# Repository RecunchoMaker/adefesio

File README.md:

# adefesio

**adefesio** intentará ser un pequeno robot para iniciarse na competición da resolución de
de labirintos. Está baseado en componentes de baixo custe (arduino, motores micrometal...)
e polo tanto a intención do proxecto non é facer un robot competitivo, senón explorar
e investigar os desfíos de programación que aparecen nesta competición.

## making off

En [Adefesio blog](https://recunchomaker.github.io/adefesio/) estamos facendo un
blog co progreso do proxecto.

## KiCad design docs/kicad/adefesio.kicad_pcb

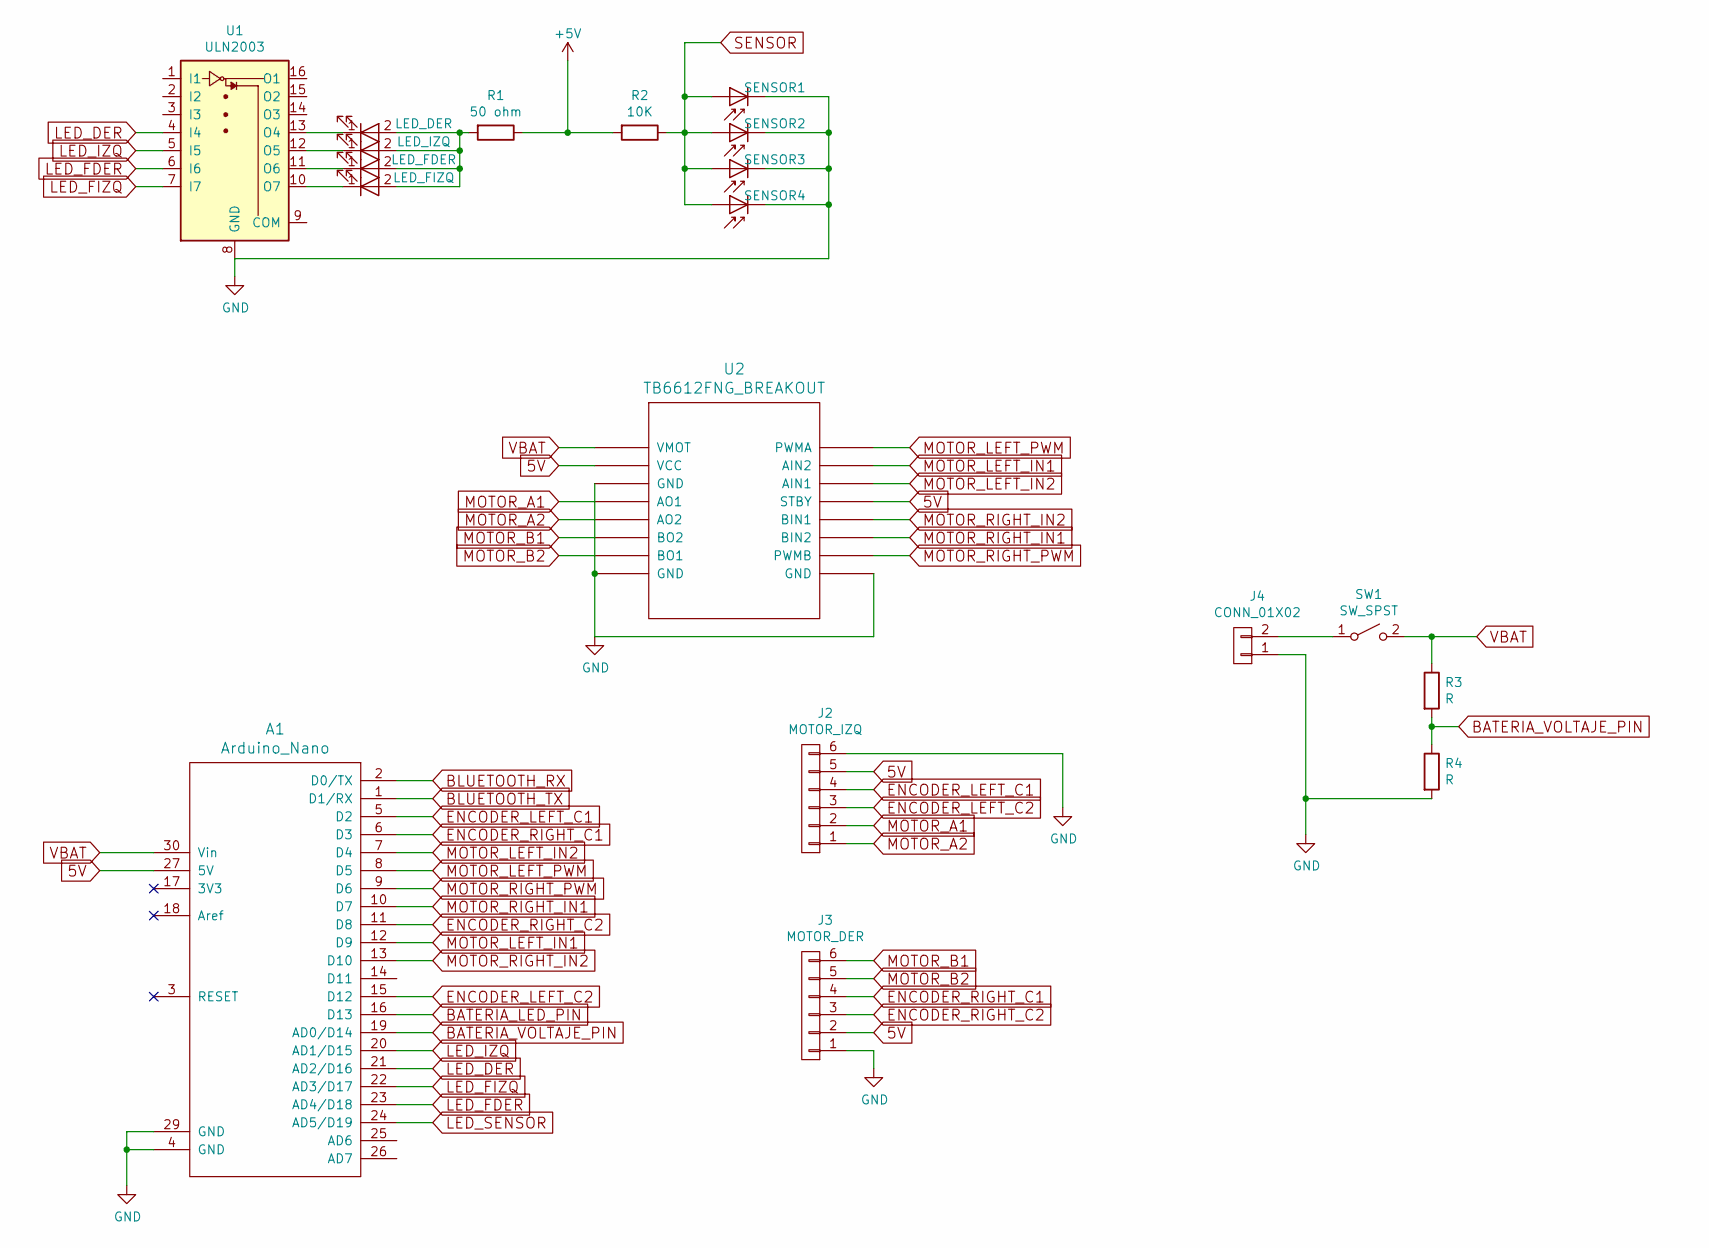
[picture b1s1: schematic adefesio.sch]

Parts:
A1: Arduino_Nano; arduino_nano
D1: LED_DER; LED_D1.8mm_W1.8mm_H2.4mm_Horizontal_O6.35mm_Z1.6mm
D2: SENSOR1; LED_D1.8mm_W1.8mm_H2.4mm_Horizontal_O3.81mm_Z1.6mm
D3: LED_IZQ; LED_D1.8mm_W1.8mm_H2.4mm_Horizontal_O6.35mm_Z1.6mm
D4: LED_FDER; LED_D1.8mm_W1.8mm_H2.4mm_Horizontal_O6.35mm_Z1.6mm
D5: LED_FIZQ; LED_D1.8mm_W1.8mm_H2.4mm_Horizontal_O6.35mm_Z1.6mm
D6: SENSOR2; LED_D1.8mm_W1.8mm_H2.4mm_Horizontal_O3.81mm_Z1.6mm
D7: SENSOR3; LED_D1.8mm_W1.8mm_H2.4mm_Horizontal_O3.81mm_Z1.6mm
D8: SENSOR4; LED_D1.8mm_W1.8mm_H2.4mm_Horizontal_O3.81mm_Z1.6mm
J2: MOTOR_IZQ; PINHEAD1-6
J3: MOTOR_DER; PINHEAD1-6
J4: CONN_01X02; PINHEAD1-2
R1: 50 ohm; R_Axial_DIN0207_L6.3mm_D2.5mm_P10.16mm_Horizontal
R2: 10K; R_Axial_DIN0207_L6.3mm_D2.5mm_P10.16mm_Horizontal
R3, R4: R; R_Axial_DIN0204_L3.6mm_D1.6mm_P7.62mm_Horizontal
SW1: SW_SPST; SW_DIP_x1_W7.62mm_Slide_Copal_CHS-B
U1: ULN2003; DIP-16_W7.62mm_LongPads
U2: TB6612FNG_BREAKOUT; DIP-16_600

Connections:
5V: A1.27 (5V), J2.5, J3.2, U2.2 (VCC), U2.13 (STBY)
+5V: R1.1, R2.2
BATERIA_LED_PIN: A1.16 (D13)
BATERIA_VOLTAJE_PIN: A1.19 (AD0/D14), R3.2, R4.1
BLUETOOTH_RX: A1.2 (D0/TX)
BLUETOOTH_TX: A1.1 (D1/RX)
ENCODER_LEFT_C1: A1.5 (D2), J2.4
ENCODER_LEFT_C2: A1.15 (D12), J2.3
ENCODER_RIGHT_C1: A1.6 (D3), J3.4
ENCODER_RIGHT_C2: A1.11 (D8), J3.3
GND: A1.4 (GND), A1.29 (GND), D2.1 (K), D6.1 (K), D7.1 (K), D8.1 (K), J2.6, J3.1, J4.1, R4.2, U1.8 (GND), U2.3 (GND), U2.8 (GND), U2.9 (GND)
LED_DER: A1.21 (AD2/D16), U1.4 (I4)
LED_FDER: A1.23 (AD4/D18), U1.6 (I6)
LED_FIZQ: A1.22 (AD3/D17), U1.7 (I7)
LED_IZQ: A1.20 (AD1/D15), U1.5 (I5)
LED_SENSOR: A1.24 (AD5/D19)
MOTOR_A1: J2.2, U2.4 (AO1)
MOTOR_A2: J2.1, U2.5 (AO2)
MOTOR_B1: J3.6, U2.6 (BO2)
MOTOR_B2: J3.5, U2.7 (BO1)
MOTOR_LEFT_IN1: A1.12 (D9), U2.15 (AIN2)
MOTOR_LEFT_IN2: A1.7 (D4), U2.14 (AIN1)
MOTOR_LEFT_PWM: A1.8 (D5), U2.16 (PWMA)
MOTOR_RIGHT_IN1: A1.10 (D7), U2.11 (BIN2)
MOTOR_RIGHT_IN2: A1.13 (D10), U2.12 (BIN1)
MOTOR_RIGHT_PWM: A1.9 (D6), U2.10 (PWMB)
unnamed: D1.1 (K), U1.13 (O4)
unnamed: D1.2 (A), D3.2 (A), D4.2 (A), D5.2 (A), R1.2
unnamed: D3.1 (K), U1.12 (O5)
unnamed: D4.1 (K), U1.11 (O6)
unnamed: D5.1 (K), U1.10 (O7)
unnamed: J4.2, SW1.1 (A)
SENSOR: D2.2 (A), D6.2 (A), D7.2 (A), D8.2 (A), R2.1
VBAT: A1.30 (Vin), R3.1, SW1.2 (B), U2.1 (VMOT)

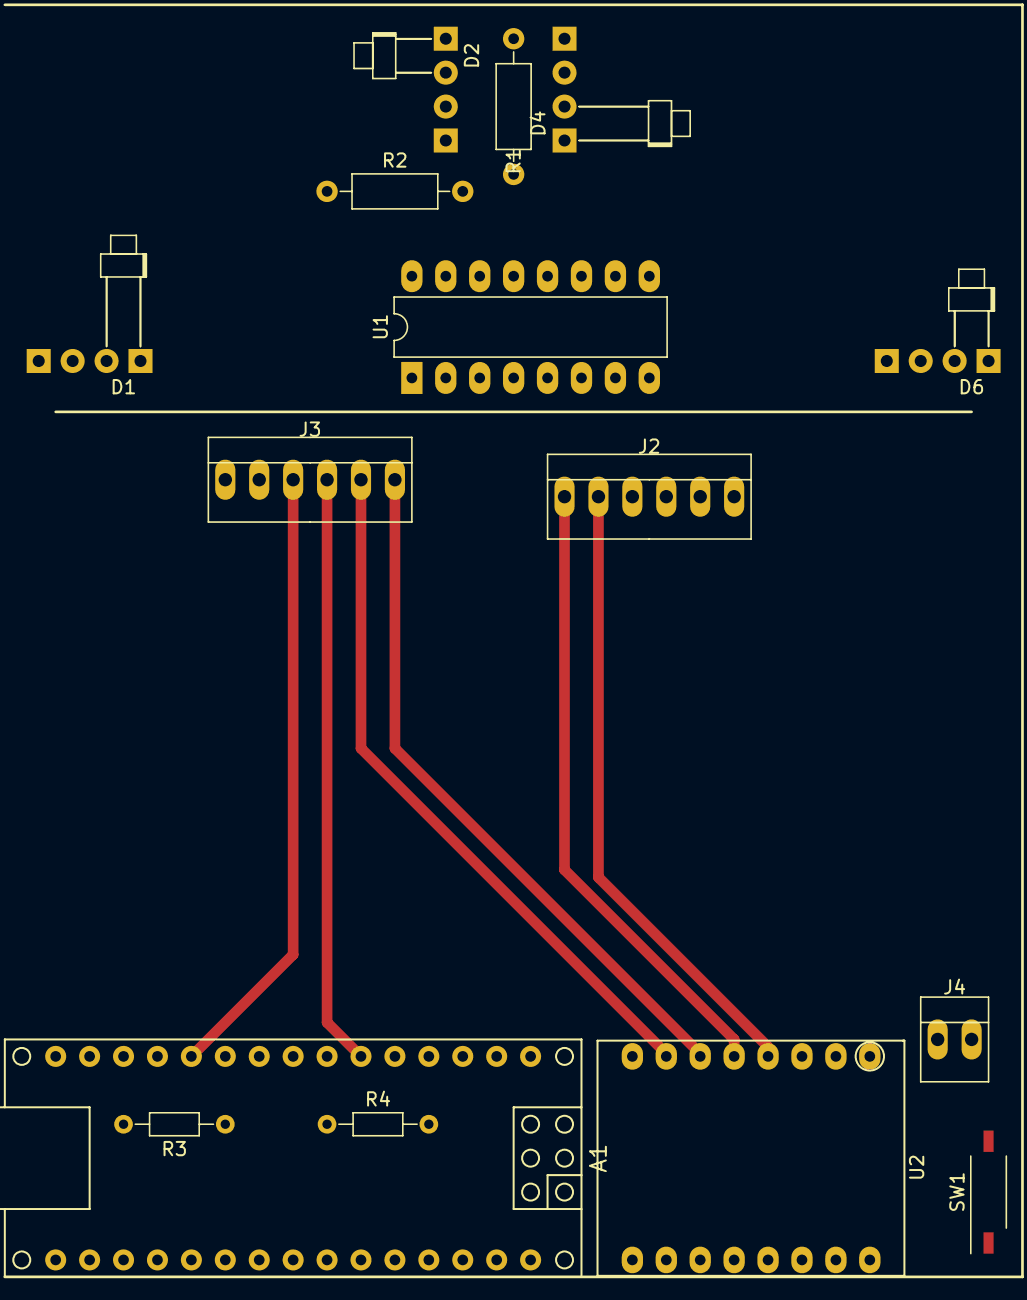
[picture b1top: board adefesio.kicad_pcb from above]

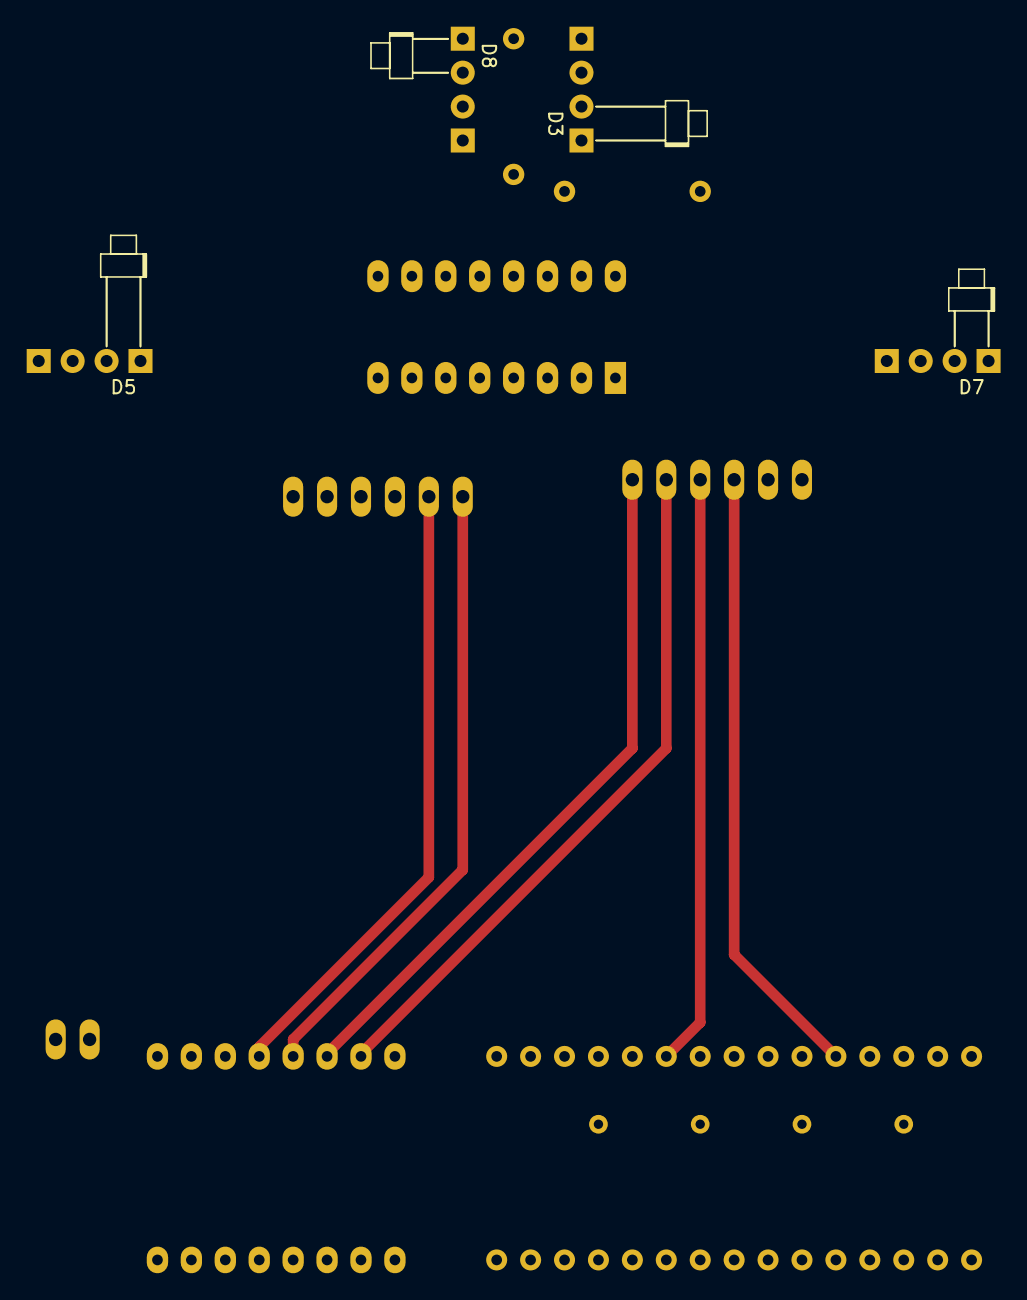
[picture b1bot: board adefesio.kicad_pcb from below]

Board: 2 copper layers, 19 parts (4 on the bottom side), 30 nets.

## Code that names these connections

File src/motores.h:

/**
 * @file motores.h
 *
 * @brief Cabecera de motores.cpp
 */

#ifndef __MOTORES_H
#define __MOTORES_H

#include <encoders.h>

//@{
/**
 * @name Pins del puente H
 */

#define MOTOR_LEFT_PWM 5   ///< Pin digital de salida PWM izquierdo 
#define MOTOR_LEFT_IN1 4   ///< Pin digital de salida IN1 izquierdo 
#define MOTOR_LEFT_IN2 9   ///< Pin digital de salida IN1 izquierdo 

#define MOTOR_RIGHT_PWM 6  ///< Pin digital de salida PWM izquierdo 
#define MOTOR_RIGHT_IN1 7  ///< Pin digital de salida IN1 derecho
#define MOTOR_RIGHT_IN2 10 ///< Pin digital de salida IN2 derecho
//@}

// TODO: fix this
#define GIRO_IZQUIERDA_TODO 0
#define GIRO_DERECHA_TODO   0.01

void motores_init(float voltaje);
void motores_set_potencia(float left, float right);
void motores_set_pwm_left(int16_t right);
void motores_set_pwm_right(int16_t left);
void motores_parar();
void motores_actualiza_velocidad();

float motores_get_kp_lineal();
void motores_set_kp_lineal(float kp);
float motores_get_ki_lineal();
void motores_set_ki_lineal(float ki);
float motores_get_kd_lineal();
void motores_set_kd_lineal(float kd);
float motores_get_kp_pasillo1();
void motores_set_kp_pasillo1(float kd);
float motores_get_kp_pasillo2();
void motores_set_kp_pasillo2(float kd);

float motores_get_velocidad_lineal_objetivo();
float motores_get_velocidad_lineal_objetivo_left();
float motores_get_velocidad_lineal_objetivo_right();
float motores_get_radio();
void motores_set_velocidad_lineal_objetivo(float velocidad);

int16_t motores_get_pwm_left();
int16_t motores_get_pwm_right();

void motores_set_maximo_pwm(int16_t pwm);
float motores_get_velocidad_angular_objetivo();
float motores_get_distancia_entre_ruedas();
void motores_set_distancia_entre_ruedas(float dr);

float motores_get_aceleracion_lineal();
void motores_set_aceleracion_lineal(float aceleracion);

void motores_set_radio(float r);

#endif /* ifndef MOTORES_H

 */

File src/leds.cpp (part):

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 * @brief Funciones para controlar los leds/sensores infrarrojos
 *
 * Los leds infrarrojos se controlan individualmente, cada uno con un
 * pin digital de salida, y hay un único sensor de entrada en un pin analógico. 
 *
 * Los pins que activan los diodos digitales deben ser adyacentes en el procesador, 
 * para facilitar la aritmética a la hora de almacenar valores en los arrays.
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
void leds_init() {

    pinMode(LED_IZQ, OUTPUT);
    pinMode(LED_DER, OUTPUT);
    pinMode(LED_FIZQ, OUTPUT);
    pinMode(LED_FDER, OUTPUT);

    pinMode(LED_SENSOR, INPUT);

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
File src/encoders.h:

/**
 * @file encoders.h
 *
 * @brief Cabecera de encoders.cpp
 */

#ifndef __ENCODERS_H
#define __ENCODERS_H

#include <Arduino.h>

#define ENCODER_LEFT_C1 2
#define ENCODER_LEFT_C2 12
#define ENCODER_RIGHT_C1 3
#define ENCODER_RIGHT_C2 8

void encoders_init(void);

void encoders_reset_posicion(void);
void encoders_reset_posicion_total(void);
void encoders_reset_posicion_aux_total(void);
void encoders_decrementa_posicion_total(int16_t pasos);

int32_t encoders_get_posicion_total_left(void);
int32_t encoders_get_posicion_total_right(void);
int32_t encoders_get_posicion_aux_left(void);
int32_t encoders_get_posicion_aux_right(void);
int32_t encoders_get_posicion_aux(void);

uint8_t encoders_get_ticks_sin_actualizar_left(void);
uint8_t encoders_get_ticks_sin_actualizar_right(void);
uint16_t encoders_get_tcnt1_anterior_right();
uint16_t encoders_get_ultimo_tcnt1_right();

float encoders_get_velocidad_left(void);
float encoders_get_velocidad_right(void);
float encoders_get_ultima_velocidad_left(void);
float encoders_get_ultima_velocidad_right(void);

int32_t encoders_get_posicion_total(void);
void encoders_set_direccion(bool left, bool right);

void encoders_ISR_left(void);
void encoders_ISR_right(void);

void encoders_calcula_velocidad();

#endif /* ifndef _ENCODERS_H

 */

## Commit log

2018-12-26 primeiro commit
2018-12-27 Set theme jekyll-theme-slate
2018-12-27 introduccion
2018-12-27 barryclark/jekyll-now skeleton
2018-12-27 config customization
2018-12-27 fixed bash tag
2018-12-27 change syntax highlight
2018-12-27 fixed double box on snippet boxes
2018-12-27 fix build failure
2018-12-27 blog 2018-12-27 Preparando el entorno con platform.io
2018-12-28 anadido control de pwm
2018-12-28 blog 2018-12-28 Motores y puente H
2018-12-28 motores y puente h
2018-12-28 motores y puente h. fixed file extension
2018-12-29 lipo y chasis
2018-12-29 blog 2018-12-29 LiPo y Chasis
2018-12-29 fixed style.scss
2018-12-29 fixed image path
2018-12-29 fix images
2018-12-30 control de bateria
2018-12-30 2018-12-30 Control de bateria
2018-12-31 envio de datos por bluetooth
2019-01-01 conexion bluetooth desde consola
2019-01-01 fixing dates
2019-01-02 2018-12-02 Control de los encoders
2019-01-02 control de encoders
2019-01-03 timers en atmega328p
2019-01-03 2019-01-03 Timers en Atmega328p
2019-01-04 2019-01-04 Controlando la velocidad
2019-01-04 controlando la velocidad
2019-01-05 2019-01-05 Controlando la velocidad - caso 1
2019-01-05 controlando la velocidad - caso 1
2019-01-06 controlando la velocidad - caso 2
2019-01-06 2019-01-06 Controlando la velocidad - caso 2
2019-01-07 2019-01-06 Controlando la velicidad - caso 3
2019-01-07 controlando la velocidad - caso 3
2019-01-08 2019-01-08 PID basico
2019-01-08 pid basico
2019-01-09 2019-01-09 Graficas con gnuplot
2019-01-09 graficas con gnuplot
2019-01-10 2019-01-10 Muchas pruebas y graficos
2019-01-10 muchas pruebas y graficos
2019-01-11 2019-01-11 Introduciendo velocidad angular
2019-01-11 introduciendo velocidad angular
2019-01-12 2019-01-11 Unidades internacionales
2019-01-12 unidades internacionales
2019-01-13 jekyll local
2019-01-14 2019-01-12 Principios de aceleracion
2019-01-14 principios de aceleracion
2019-01-15 lagom theme
2019-01-17 2019-01-16 Revisitando velocidad
2019-01-17 revisitando velocidad
2019-01-17 2019-01-17 Constante KA en pid
2019-01-17 constante ka en pid
2019-01-17 2019-01-18 Filtro Kalman
2019-01-17 filtro Kalman
2019-01-19 2019-01-19 Revisitando velocidad angular
2019-01-19 revisitando velocidad angular
2019-01-20 2019-01-20 Girando sobre si mismo
2019-01-20 girando sobre si mismo
2019-01-21 2019-01-21 Angulo solo con pasos
2019-01-21 angulo solo con pasos
2019-01-22 2019-01-22 Posicion del robot
2019-01-22 posicion del robot
2019-01-23 2019-01-23 Logeando PID en tiempo real
2019-01-23 logeando pid en tiempo real
2019-01-24 2019-01-24 Afinando el pid
2019-01-24 afinando el pid
2019-01-25 2019-01-25 Calibrando pwm segun bateria
2019-01-25 normalizar pwm en funcion de bateria
2019-01-26 2019-01-26 Interprete de comandos sencillo
2019-01-26 interprete de comandos sencillo
2019-01-27 flujo de trabajo con interprete de comandos
2019-01-28 2019-01-28 Velocidad maxima y de nuevo aceleracion
2019-01-28 velocidad maxima y de nuevo aceleracion
2019-01-29 2019-01-29 Decelerando
2019-01-29 decelerando
2019-01-30 2019-01-30 Girando con deceleracion
2019-01-30 girando con deceleracion
2019-01-31 2019-01-31 Unas paredes de contrachapado
2019-01-31 unas paredes de contrachapado
2019-02-01 2019-02-01 Haciendo circulos
2019-02-01 haciendo circulos
2019-02-02 2019-02-02 Velocidad maxima de giro
2019-02-02 velocidad maxima de giro
2019-02-03 2019-02-03 Control de aceleraciones en el timer
2019-02-03 control de aceleraciones en el timer
2019-02-04 2019-02-04 Refactorizando secuencias
2019-02-04 refactorizando secuencias
2019-02-05 2018-02-05 Depurando trayectorias
2019-02-05 depurando trayectorias
2019-02-06 2019-02-06 Error en el calculo de sentido
2019-02-06 error en el calculo de sentido
2019-02-07 2019-02-07 Terminologia. Acciones y secuencias
2019-02-07 terminologia acciones y secuencias
2019-02-08 2019-02-08 Bugs en robot.cpp
2019-02-08 bugs en robot.cpp
2019-02-09 2019-02-09 Ultimo retoque a la trayectoria
2019-02-09 ultimo retoque a la trayectoria
2019-02-10 2019-02-10 Terminamos con los motores
2019-02-10 terminamos con los motores
2019-02-11 un sensor infrarrojo
2019-02-12 2019-02-11 Encendiendo y apagando
2019-02-12 encendiendo y apagando
2019-02-13 2019-02-12 Repartiendo el trabajo
2019-02-13 repartiendo trabajo
2019-02-14 2019-02-13 Leyendo el sensor
2019-02-14 leyendo el sensor
2019-02-15 2019-02-15 Compartir pin de lectura
2019-02-15 compartir pin de lectura
2019-02-16 2019-02-16 Modulo de sensores en kicad
2019-02-16 modulo de sensores en kicad
2019-02-17 soldando modulo de sensores
2019-02-18 2019-18-02 Chasis para sensores
2019-02-18 chasis para sensores
2019-02-19 2019-02-19 Procastinando
2019-02-19 procastinando
2019-02-21 soldando poco a poco
2019-02-22 2019-02-22 Ultima pieza
2019-02-22 ultima pieza
2019-02-24 2019-02-24 Ajustando posicion de sensores
2019-02-24 ajustando posicion de sensores
2019-02-25 2019-02-25 Segmento en recta y parar
2019-02-25 segmento en recta y parar
2019-02-26 2019-02-26 Guardando el laberinto
2019-02-26 guardando el laberinto
2019-02-27 mas madera
2019-02-28 2019-02-28 Encaje de viguetas y paredes
2019-02-28 encaje viguetas y paredes
2019-03-01 2019-03-01 Ruido en sensores
2019-03-01 ruido en los sensores
2019-03-02 2019-03-02 No hay ruido en los sensores
2019-03-02 no hay ruido en los sensores
2019-03-03 2019-03-03 Casilla offset
2019-03-03 casilla offset
2019-03-04 Detectando casilla
2019-03-05 2019-03-05 Errores varios
2019-03-05 errores varios
2019-03-06 2019-03-06 Mano derecha 1 de ...
2019-03-06 mano derecha 1
2019-03-07 Mano derecha 2 de ...
2019-03-07 mano derecha 2
2019-03-08 2019-03-08 Mano derecha 3 de 3 y mapeando correctamente
2019-03-08 mano derecha 3 de 3 y mapeando correctamente
2019-03-09 2019-03-09 Refactorizando accion
2019-03-09 refactorizando accion
2019-03-10 2019-03-10 Documentando con Doxygen
2019-03-10 documentando con doxygen
2019-03-11 2019-03-11 Continua la documentacion
2019-03-11 continua la documentacion
2019-03-12 Cambio en logs
2019-03-13 2019-03-13 Terminando con accio y robot. Y Makefile
2019-03-13 terminando con accion y robot - makefile
2019-03-14 Documentando motores y encoders
2019-03-15 2019-03-15 Empezando con FloodFill
2019-03-15 empezando con flood fill
2019-03-16 2019-03-16 Log enorme de sensores
2019-03-16 log enorme de sensores
2019-03-17 2019-03-17 Anaddo script extrae_acciones_Log
2019-03-19 Problema grave en sensores
2019-03-19 2019-03-19 ...y posible solución
2019-03-19 posible solucion
2019-03-20 resoldando
2019-03-20 2019-03-20 pid entre paredes
2019-03-20 pid entre paredes
2019-03-21 2019-03-21 Eliminando fila y columna dummy
2019-03-21 eliminado fila columna dummy
2019-03-22 2019-03-22 y la volvemos a poner
2019-03-22 y la volvemos a poner
2019-03-23 2019-03-23 Caminos
2019-03-23 caminos
2019-03-24 2019-03-24 Siguiendo un camino
2019-03-24 siguiendo un camino
2019-03-25 2019-03-25 Valor medio en leds
2019-03-26 2019-03-26 Calcular la distancia con los sensores
2019-03-26 calcular la distancia con los sensores
2019-03-27 Valores de led en segmentos
2019-03-28 2019-03-28 Recuperar la linea central - 1
2019-03-28 recuperar la linea central
2019-03-29 2019-03-29 intantando correccion angulo - broken
2019-03-30 2019-03-29 Recuperar la linea central -2
2019-03-30 recuperar la linea central - 2
2019-03-30 Calculando caminos
2019-03-31 2019-03-31 Minima distancia en leds
2019-03-31 minima distancia en leds
2019-04-01 2019-04-01 Sincronizando con minimos
2019-04-01 sincronizando con minimos
2019-04-02 2019-04-02 Desplazamientos laterales
2019-04-03 Primer laberinto completado
2019-04-04 2019-03-04 casi casi
2019-04-05 pre arduino day
2019-04-08 limpieza de logs y eliminacion de control en giros
2019-04-08 fin primera parte
2019-04-09 mejor calculo de camino
2019-04-10 empezando mock para mms
2019-04-11 mock casi funcional
2019-04-12 mock funcional
2019-04-13 anadido log para desvio en pasillos
2019-04-14 empezando calibracion automatica
2019-04-15 graba y lee segmentos en eeprom
2019-04-16 calibrando pasillo
2019-04-17 refactorizando funciones de control a fichero propio
2019-04-20 prueba calibracion diodos laterales
2019-04-22 tunning distancias para calibracion en pasillos
2019-04-22 extraer de robot.cpp el control en avance
2019-04-22 sincronizacion de final de casilla con fin o principio de pared
2019-04-23 mejor correccion en parada ante muro
2019-04-26 arreglado flood despues de romperlo con funciones de control
